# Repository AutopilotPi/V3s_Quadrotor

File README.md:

### 简介

这是一个参考的AutopilotPI载板，包括：
- ov2640摄像头接口
- ESP32及其下载电路
  - 其中esp32的sdio接口与AutopilotPI相连，v3s可以通过sdio接口控制esp32作为sdio网卡，实测延迟比较高（80ms+），后放弃
  - ov2640摄像头接口与esp32 I2S相连，未测试
- E32-900M20S（SX1280模块）（可用于制作900M ELRS）
  - 未测试
- ea3036三路dcdc电路
- 1S锂电池充电/升压电路
- 4路空心杯驱动电路
  
### Images

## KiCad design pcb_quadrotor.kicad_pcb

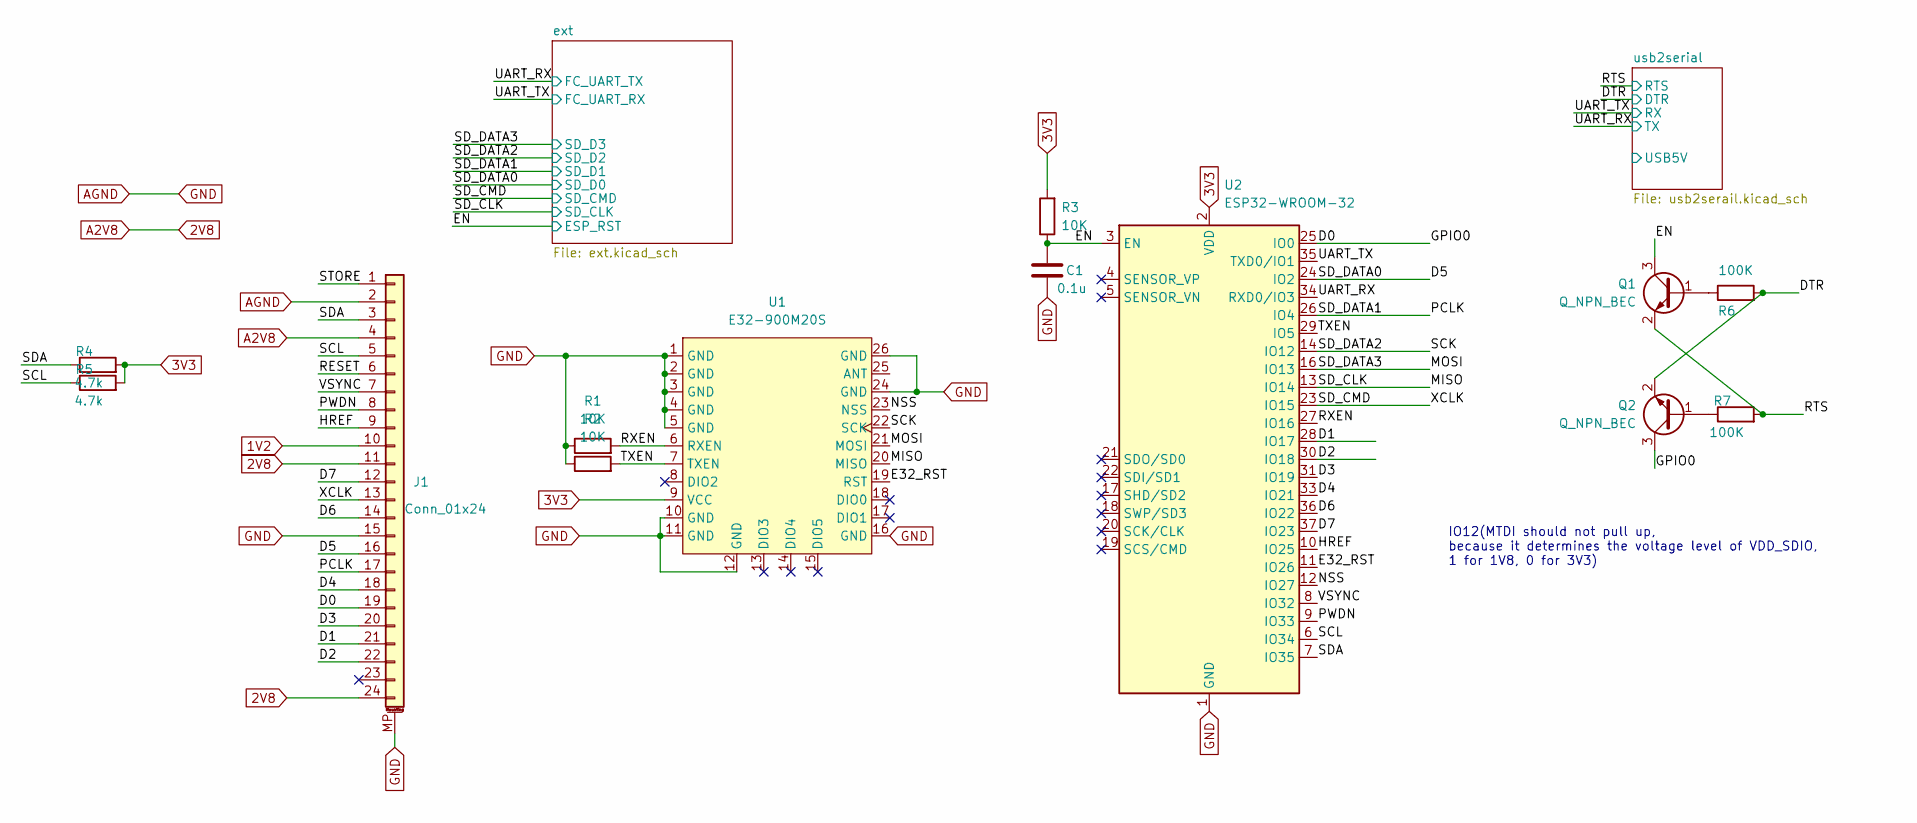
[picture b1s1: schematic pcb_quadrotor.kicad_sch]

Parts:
C1: 0.1u; C_0603_1608Metric
J1: Conn_01x24; Hirose_FH12-24S-0.5SH_1x24-1MP_P0.50mm_Horizontal
Q1, Q2: Q_NPN_BEC; TSOT-23
R1, R2, R3: 10K; R_0603_1608Metric
R4, R5: 4.7k; R_0603_1608Metric
R6, R7: 100K; R_0603_1608Metric
U1: E32-900M20S
U2: ESP32-WROOM-32

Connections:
1V2: J1.10; also elsewhere on the board
2V8: J1.4, J1.11, J1.24; also elsewhere on the board
3V3: R3.2, R4.2, R5.2, U1.9 (VCC), U2.2 (VDD); also elsewhere on the board
/D0: J1.19, Q2.3 (C), U2.25 (IO0)
/D1: J1.21, U2.28 (IO17)
/D2: J1.22, U2.30 (IO18)
/D3: J1.20, U2.31 (IO19)
/D4: J1.18, U2.33 (IO21)
/D5: J1.16, U2.24 (IO2); also elsewhere on the board
/D6: J1.14, U2.36 (IO22)
/D7: J1.12, U2.37 (IO23)
/DTR: Q2.2 (E), R6.2; also elsewhere on the board
/E32_RST: U1.19 (RST), U2.11 (IO26)
/EN: C1.1, Q1.3 (C), R3.1, U2.3 (EN); also elsewhere on the board
/HREF: J1.9, U2.10 (IO25)
/MISO: U1.20 (MISO), U2.13 (IO14); also elsewhere on the board
/MOSI: U1.21 (MOSI), U2.16 (IO13); also elsewhere on the board
/NSS: U1.23 (NSS), U2.12 (IO27)
/PCLK: J1.17, U2.26 (IO4); also elsewhere on the board
/PWDN: J1.8, U2.9 (IO33)
/RESET: J1.6
/RTS: Q1.2 (E), R7.2; also elsewhere on the board
/RXEN: R1.2, U1.6 (RXEN), U2.27 (IO16)
/SCK: U1.22 (SCK), U2.14 (IO12); also elsewhere on the board
/SCL: J1.5, R5.1, U2.6 (IO34)
/SDA: J1.3, R4.1, U2.7 (IO35)
/SD_CMD: J1.13, U2.23 (IO15); also elsewhere on the board
/STORE: J1.1
/TXEN: R2.2, U1.7 (TXEN), U2.29 (IO5)
/UART_RX: U2.34 (RXD0/IO3); also elsewhere on the board
/UART_TX: U2.35 (TXD0/IO1); also elsewhere on the board
/VSYNC: J1.7, U2.8 (IO32)
AGND: C1.2, J1.2, J1.15, J1.MP (MountPin), R1.1, R2.1, U1.1 (GND), U1.2 (GND), U1.3 (GND), U1.4 (GND), U1.5 (GND), U1.10 (GND), U1.11 (GND), U1.12 (GND), U1.16 (GND), U1.24 (GND), U1.26 (GND), U2.1 (GND), U2.15 (GND), U2.38 (GND), U2.39 (GND); also elsewhere on the board
unnamed: Q1.1 (B), R6.1
unnamed: Q2.1 (B), R7.1

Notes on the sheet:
IO12(MTDI should not pull up, because it determines the voltage level of VDD_SDIO, 1 for 1V8, 0 for 3V3)

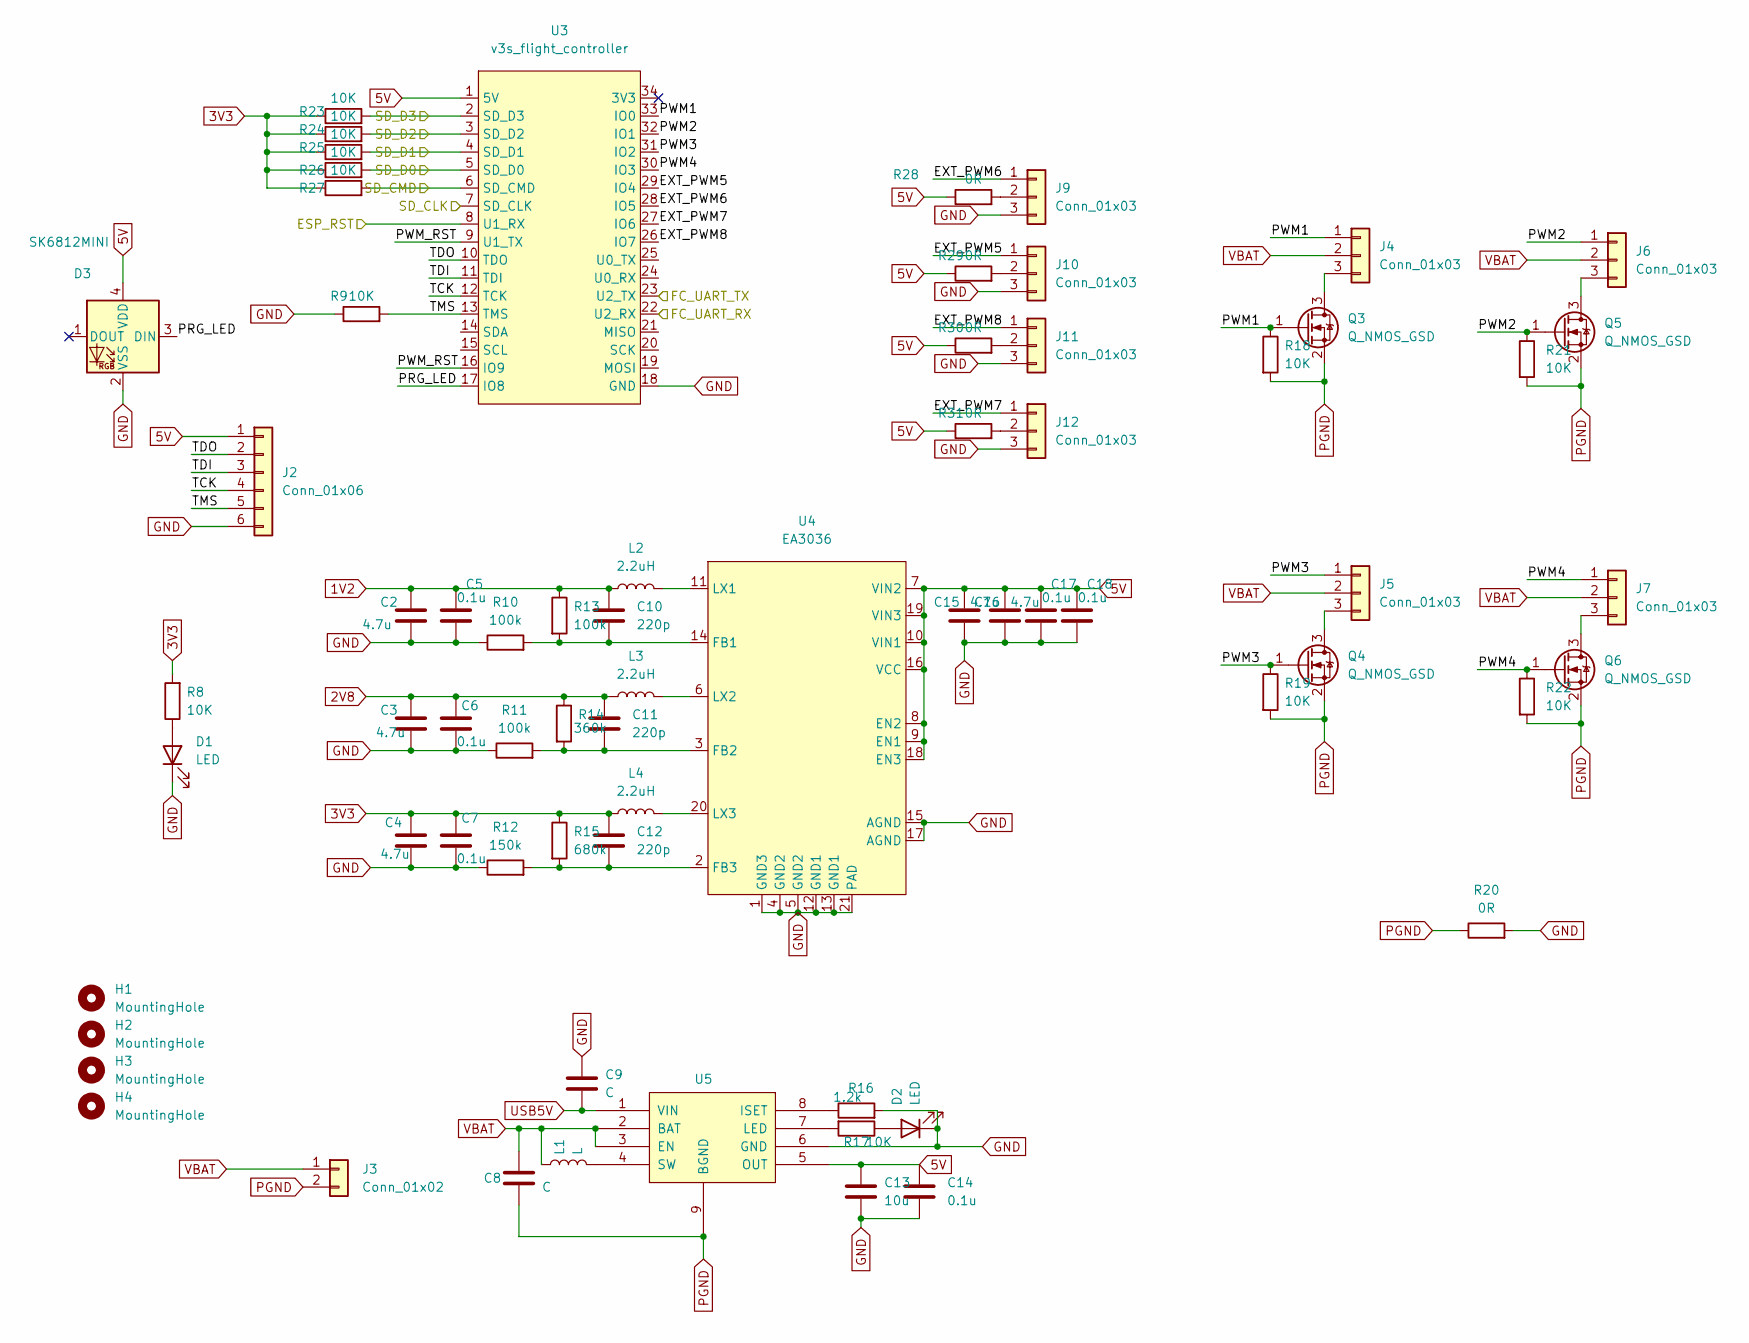
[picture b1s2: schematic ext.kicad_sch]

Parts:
C2, C3, C4, C15, C16: 4.7u; C_0603_1608Metric
C5, C6, C7, C14, C17, C18: 0.1u; C_0603_1608Metric
C8, C9: C; C_0805_2012Metric
C10, C11, C12: 220p; C_0603_1608Metric
C13: 10u; C_0805_2012Metric
D1, D2: LED; LED_0805_2012Metric
D3: SK6812MINI; LED_SK6812MINI_PLCC4_3.5x3.5mm_P1.75mm
H1, H2, H3, H4: MountingHole; MountingHole_3.2mm_M3
J2: Conn_01x06; PinHeader_1x06_P2.54mm_Vertical
J3: Conn_01x02; PinHeader_1x02_P2.54mm_Vertical
J4, J5, J6, J7, J9, J10, J11, J12: Conn_01x03; PinHeader_1x03_P2.54mm_Vertical
L1: L; L_Abracon_ASPI-3012S
L2, L3, L4: 2.2uH; L_Abracon_ASPI-3012S
Q3, Q4, Q5, Q6: Q_NMOS_GSD; SOT-23
R8, R9, R17, R18, R19, R21, R22, R23, R24, R25, R26, R27: 10K; R_0603_1608Metric
R10, R11, R13: 100k; R_0603_1608Metric
R12: 150k; R_0603_1608Metric
R14: 360k; R_0603_1608Metric
R15: 680k; R_0603_1608Metric
R16: 1.2k; R_0603_1608Metric
R20, R28, R29, R30, R31: 0R; R_0603_1608Metric
U3: v3s_flight_controller; Flight_Core
U4: EA3036; QFN-20-1EP_3x3mm_P0.4mm_EP1.65x1.65mm
U5: ETA9640; SOIC-8-1EP_3.9x4.9mm_P1.27mm_EP2.41x3.3mm

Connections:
1V2: C2.1, C5.1, C10.1, L2.1, R13.1; also elsewhere on the board
2V8: C3.1, C6.1, C11.1, L3.1, R14.1; also elsewhere on the board
3V3: C4.1, C7.1, C12.1, L4.1, R8.2, R15.1, R23.1, R24.1, R25.1, R26.1, R27.1; also elsewhere on the board
5V: C13.1, C14.1, C15.1, C16.1, C17.1, C18.1, D3.4 (VDD), J2.1, R28.1, R29.1, R30.1, R31.1, U3.1 (5V), U4.7 (VIN2), U4.8 (EN2), U4.9 (EN1), U4.10 (VIN1), U4.16 (VCC), U4.18 (EN3), U4.19 (VIN3), U5.5 (OUT); also elsewhere on the board
/D5: R26.2, U3.5 (SD_D0); also elsewhere on the board
/EN: U3.8 (U1_RX); also elsewhere on the board
/MISO: U3.7 (SD_CLK); also elsewhere on the board
/MOSI: R23.2, U3.2 (SD_D3); also elsewhere on the board
/PCLK: R25.2, U3.4 (SD_D1); also elsewhere on the board
/SCK: R24.2, U3.3 (SD_D2); also elsewhere on the board
/SD_CMD: R27.2, U3.6 (SD_CMD); also elsewhere on the board
/UART_RX: U3.23 (U2_TX); also elsewhere on the board
/UART_TX: U3.22 (U2_RX); also elsewhere on the board
/ext/EXT_PWM5: J10.1, U3.29 (IO4)
/ext/EXT_PWM6: J9.1, U3.28 (IO5)
/ext/EXT_PWM7: J12.1, U3.27 (IO6)
/ext/EXT_PWM8: J11.1, U3.26 (IO7)
/ext/PRG_LED: D3.3 (DIN), U3.17 (IO8)
/ext/PWM1: J4.1, Q3.1 (G), R18.1, U3.33 (IO0)
/ext/PWM2: J6.1, Q5.1 (G), R21.1, U3.32 (IO1)
/ext/PWM3: J5.1, Q4.1 (G), R19.1, U3.31 (IO2)
/ext/PWM4: J7.1, Q6.1 (G), R22.1, U3.30 (IO3)
/ext/PWM_RST: U3.9 (U1_TX), U3.16 (IO9)
/ext/TCK: J2.4, U3.12 (TCK)
/ext/TDI: J2.3, U3.11 (TDI)
/ext/TDO: J2.2, U3.10 (TDO)
/ext/TMS: J2.5, R9.2, U3.13 (TMS)
AGND: C2.2, C3.2, C4.2, C5.2, C6.2, C7.2, C9.1, C13.2, C14.2, C15.2, C16.2, C17.2, C18.2, D1.1 (K), D2.1 (K), D3.2 (VSS), J2.6, J9.3, J10.3, J11.3, J12.3, R9.1, R10.1, R11.1, R12.1, R16.2, R20.2, U3.18 (GND), U4.1 (GND3), U4.4 (GND2), U4.5 (GND2), U4.12 (GND1), U4.13 (GND1), U4.15 (AGND), U4.17 (AGND), U4.21 (PAD), U5.6 (GND); also elsewhere on the board
unnamed: C10.2, R10.2, R13.2, U4.14 (FB1)
unnamed: C11.2, R11.2, R14.2, U4.3 (FB2)
unnamed: C12.2, R12.2, R15.2, U4.2 (FB3)
unnamed: D1.2 (A), R8.1
unnamed: D2.2 (A), R17.1
unnamed: J4.3, Q3.3 (D)
unnamed: J5.3, Q4.3 (D)
unnamed: J6.3, Q5.3 (D)
unnamed: J7.3, Q6.3 (D)
unnamed: J9.2, R28.2
unnamed: J10.2, R29.2
unnamed: J11.2, R30.2
unnamed: J12.2, R31.2
unnamed: L1.2, U5.4 (SW)
unnamed: L2.2, U4.11 (LX1)
unnamed: L3.2, U4.6 (LX2)
unnamed: L4.2, U4.20 (LX3)
unnamed: R16.1, U5.8 (ISET)
unnamed: R17.2, U5.7 (LED)
PGND: C8.2, J3.2, Q3.2 (S), Q4.2 (S), Q5.2 (S), Q6.2 (S), R18.2, R19.2, R20.1, R21.2, R22.2, U5.9 (BGND)
USB5V: C9.2, U5.1 (VIN); also elsewhere on the board
VBAT: C8.1, J3.1, J4.2, J5.2, J6.2, J7.2, L1.1, U5.2 (BAT), U5.3 (EN)

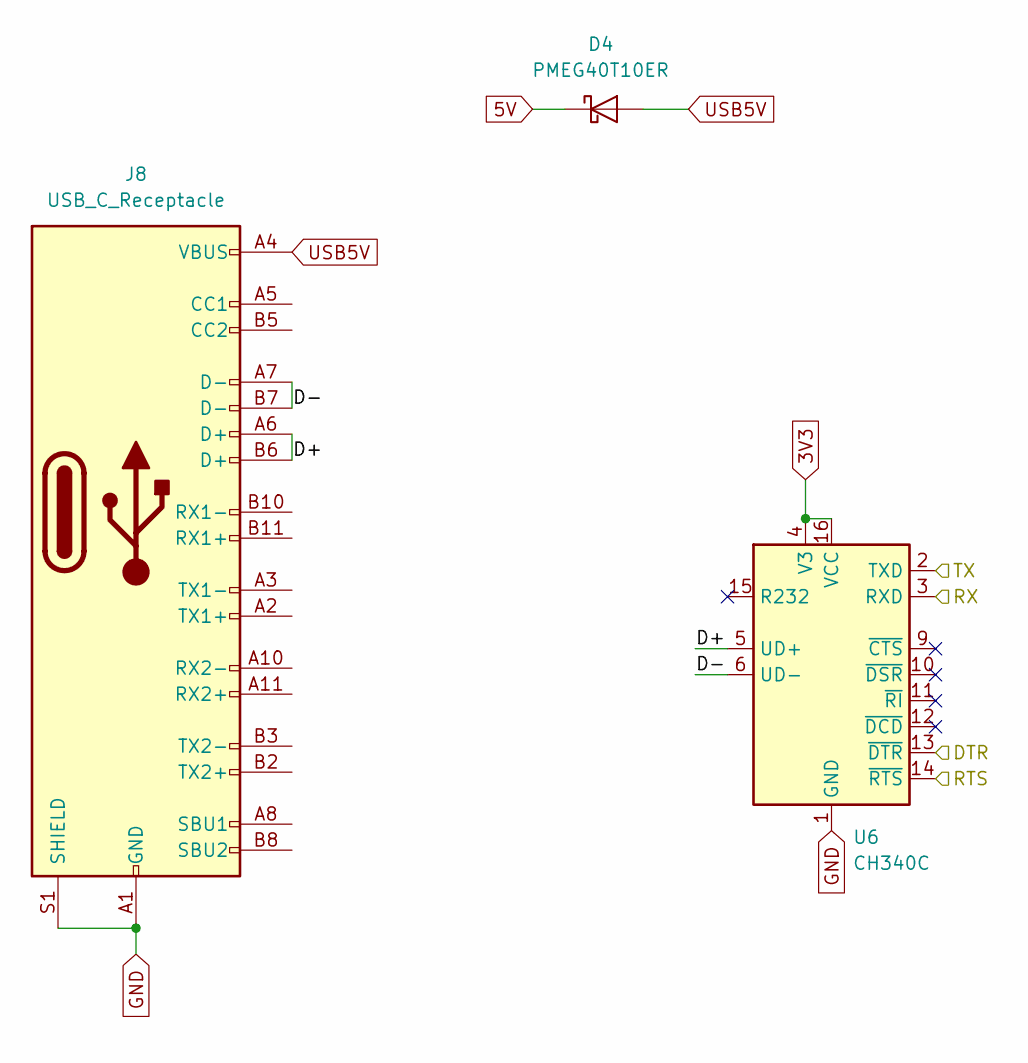
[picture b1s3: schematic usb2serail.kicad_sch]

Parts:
D4: PMEG40T10ER; Nexperia_CFP3_SOD-123W
J8: USB_C_Receptacle; USB_C_Receptacle_Palconn_UTC16-G
U6: CH340C; SOIC-16_3.9x9.9mm_P1.27mm

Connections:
3V3: U6.4 (V3), U6.16 (VCC); also elsewhere on the board
5V: D4.1 (K); also elsewhere on the board
/DTR: U6.13 (~DTR); also elsewhere on the board
/RTS: U6.14 (~RTS); also elsewhere on the board
/UART_RX: U6.2 (TXD); also elsewhere on the board
/UART_TX: U6.3 (RXD); also elsewhere on the board
/usb2serial/D+: J8.A6 (D+), J8.B6 (D+), U6.5 (UD+)
/usb2serial/D-: J8.A7 (D-), J8.B7 (D-), U6.6 (UD-)
AGND: J8.A1 (GND), J8.A12 (GND), J8.B1 (GND), J8.B12 (GND), J8.S1 (SHIELD), U6.1 (GND); also elsewhere on the board
USB5V: D4.2 (A), J8.A4 (VBUS), J8.A9 (VBUS), J8.B4 (VBUS), J8.B9 (VBUS); also elsewhere on the board

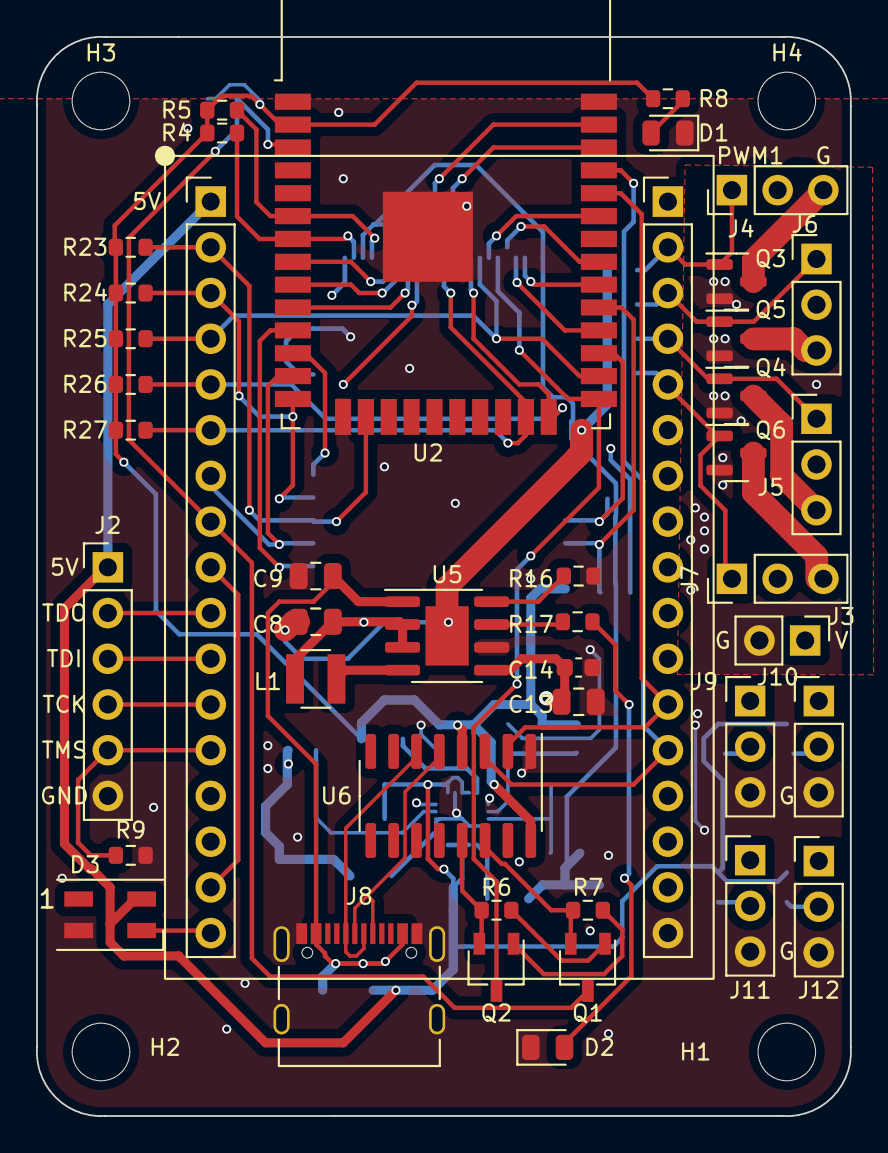
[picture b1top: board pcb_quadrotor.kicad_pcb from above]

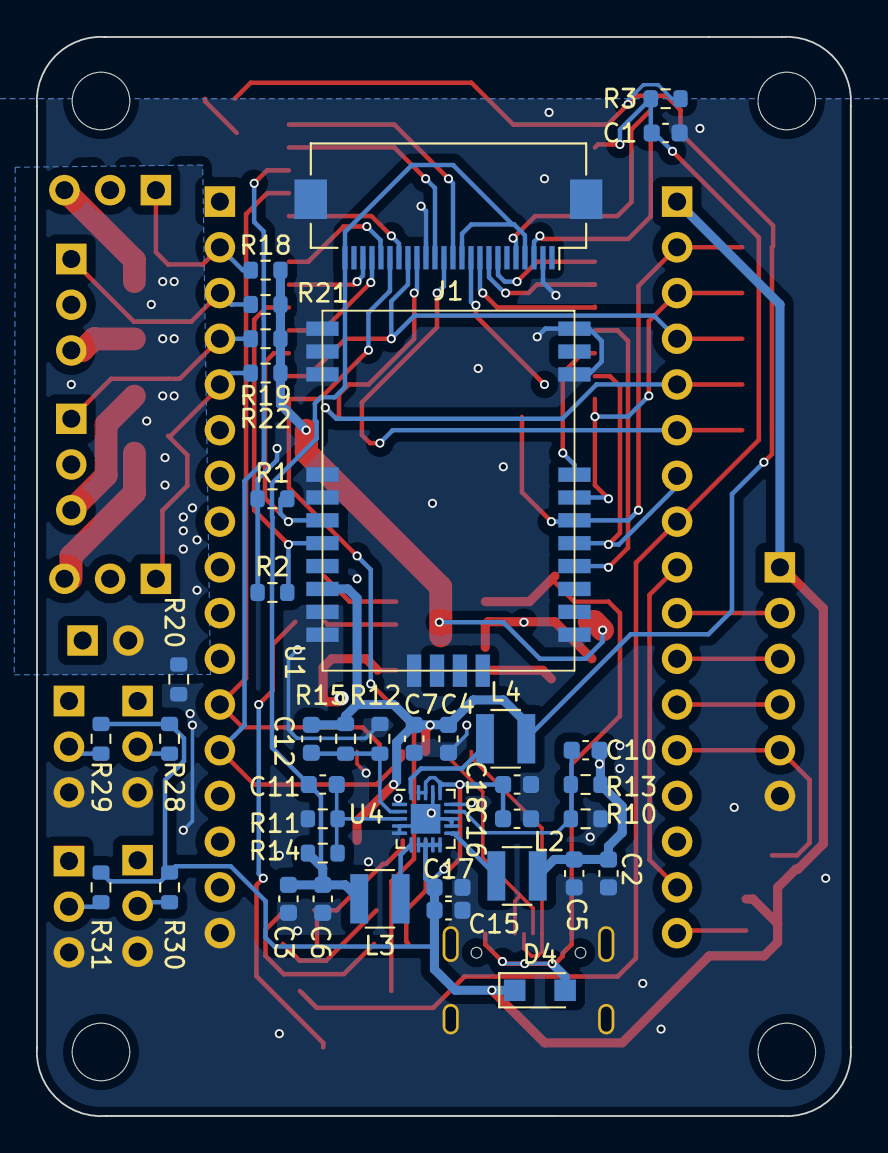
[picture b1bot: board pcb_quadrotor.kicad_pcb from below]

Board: 4 copper layers, 45.2 x 60.0 mm, 85 parts (39 on the bottom side), 72 nets.

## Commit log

2022-03-14 init
2022-06-25 add images/docs/mechanical and Readme
2022-06-25 edit images url of readme
